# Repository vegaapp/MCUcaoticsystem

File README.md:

# MCUcaoticsystem
Show Implement caotic Lorenz, Rossler and Chan oscillator in Arduino Mega 2560

In arduino code, call funtion in main loop:

Sistema_Lorez(); --> call Lorenz Oscillator

Sistema_Roosler(); --> call Rossles Oscillator

Sistema_Chen(); --> call chen Oscillator

Lorenz Oscillator

Rossles Oscillator:

chen Oscillator:

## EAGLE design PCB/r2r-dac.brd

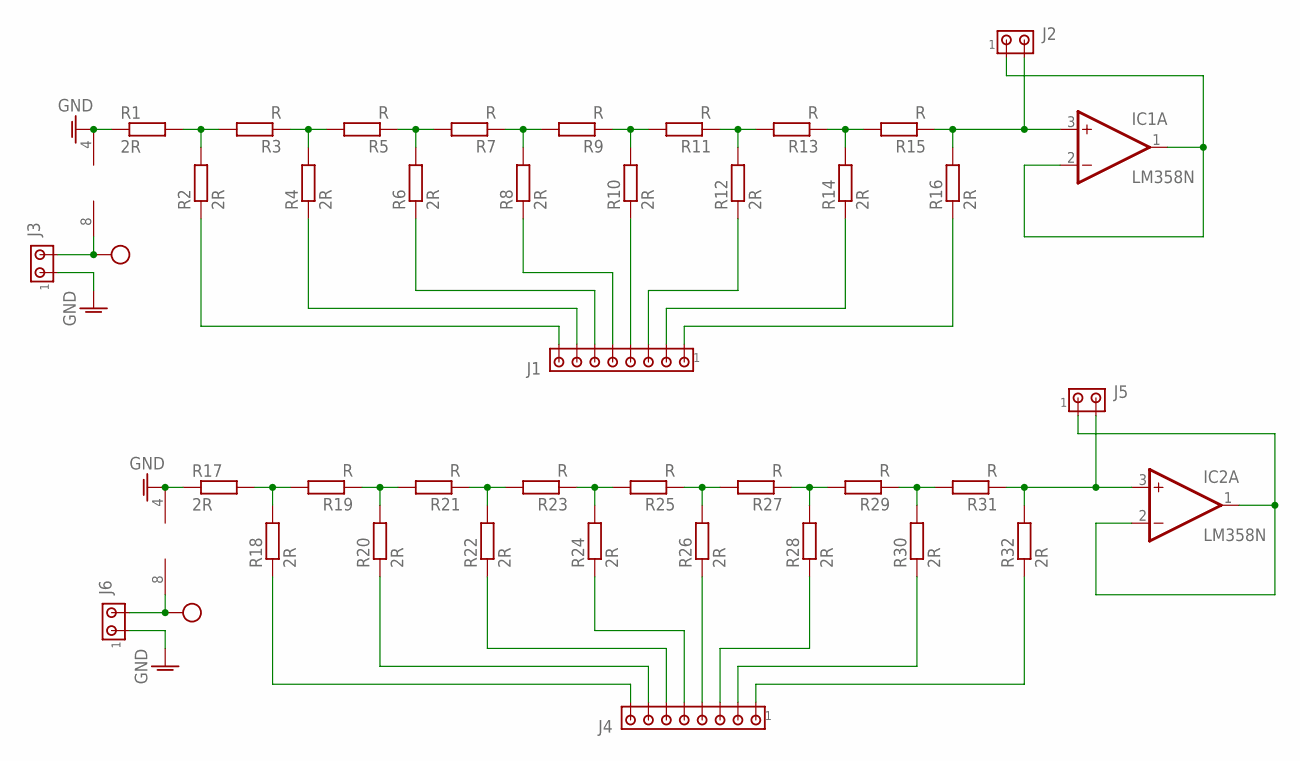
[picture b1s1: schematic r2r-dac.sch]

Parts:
IC1, IC2: LM358N; DIL08
J1, J4: MTA08-100; 10X08MTA
J2, J3, J5, J6: MTA02-100; 10X02MTA
R1, R2, R4, R6, R8, R10, R12, R14, R16, R17, R18, R20, R22, R24, R26, R28, R30, R32: 2R; 0207/10
R3, R5, R7, R9, R11, R13, R15, R19, R21, R23, R25, R27, R29, R31: R; 0207/10

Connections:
GND: IC1.4 (V-), IC2.4 (V-), J3.1, J6.1, R1.1, R17.1
unnamed: R1.2, R2.2, R3.2
unnamed: R3.1, R4.2, R5.2
unnamed: R5.1, R6.2, R7.2
unnamed: R7.1, R8.2, R9.2
unnamed: R9.1, R10.2, R11.2
unnamed: R11.1, R12.2, R13.2
unnamed: R13.1, R14.2, R15.2
unnamed: IC1.3 (+IN), J2.2, R15.1, R16.2
unnamed: J1.8, R2.1
unnamed: J1.7, R4.1
unnamed: J1.6, R6.1
unnamed: J1.5, R8.1
unnamed: J1.4, R10.1
unnamed: J1.3, R12.1
unnamed: J1.2, R14.1
unnamed: J1.1, R16.1
unnamed: R17.2, R18.2, R19.2
unnamed: IC1.1 (OUT), IC1.2 (-IN), J2.1
unnamed: R19.1, R20.2, R21.2
unnamed: R21.1, R22.2, R23.2
unnamed: R23.1, R24.2, R25.2
unnamed: R25.1, R26.2, R27.2
unnamed: R27.1, R28.2, R29.2
unnamed: R29.1, R30.2, R31.2
unnamed: IC2.3 (+IN), J5.2, R31.1, R32.2
unnamed: J4.8, R18.1
unnamed: J4.7, R20.1
unnamed: J4.6, R22.1
unnamed: J4.5, R24.1
unnamed: J4.4, R26.1
unnamed: J4.3, R28.1
unnamed: J4.2, R30.1
unnamed: J4.1, R32.1
unnamed: IC2.1 (OUT), IC2.2 (-IN), J5.1
VDD: IC1.8 (V+), IC2.8 (V+), J3.2, J6.2

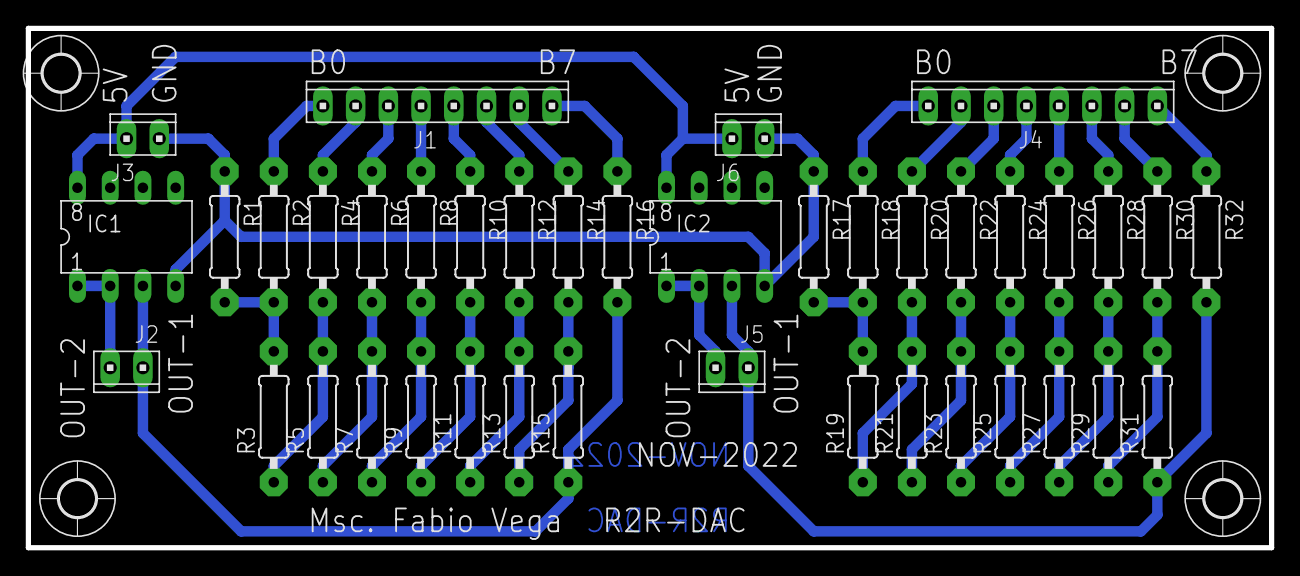
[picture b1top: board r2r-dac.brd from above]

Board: 2 copper layers, 96.5 x 40.3 mm, 44 parts (0 on the bottom side), 36 nets.

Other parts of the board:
U$1, U$2, U$3, U$4: 2,8
